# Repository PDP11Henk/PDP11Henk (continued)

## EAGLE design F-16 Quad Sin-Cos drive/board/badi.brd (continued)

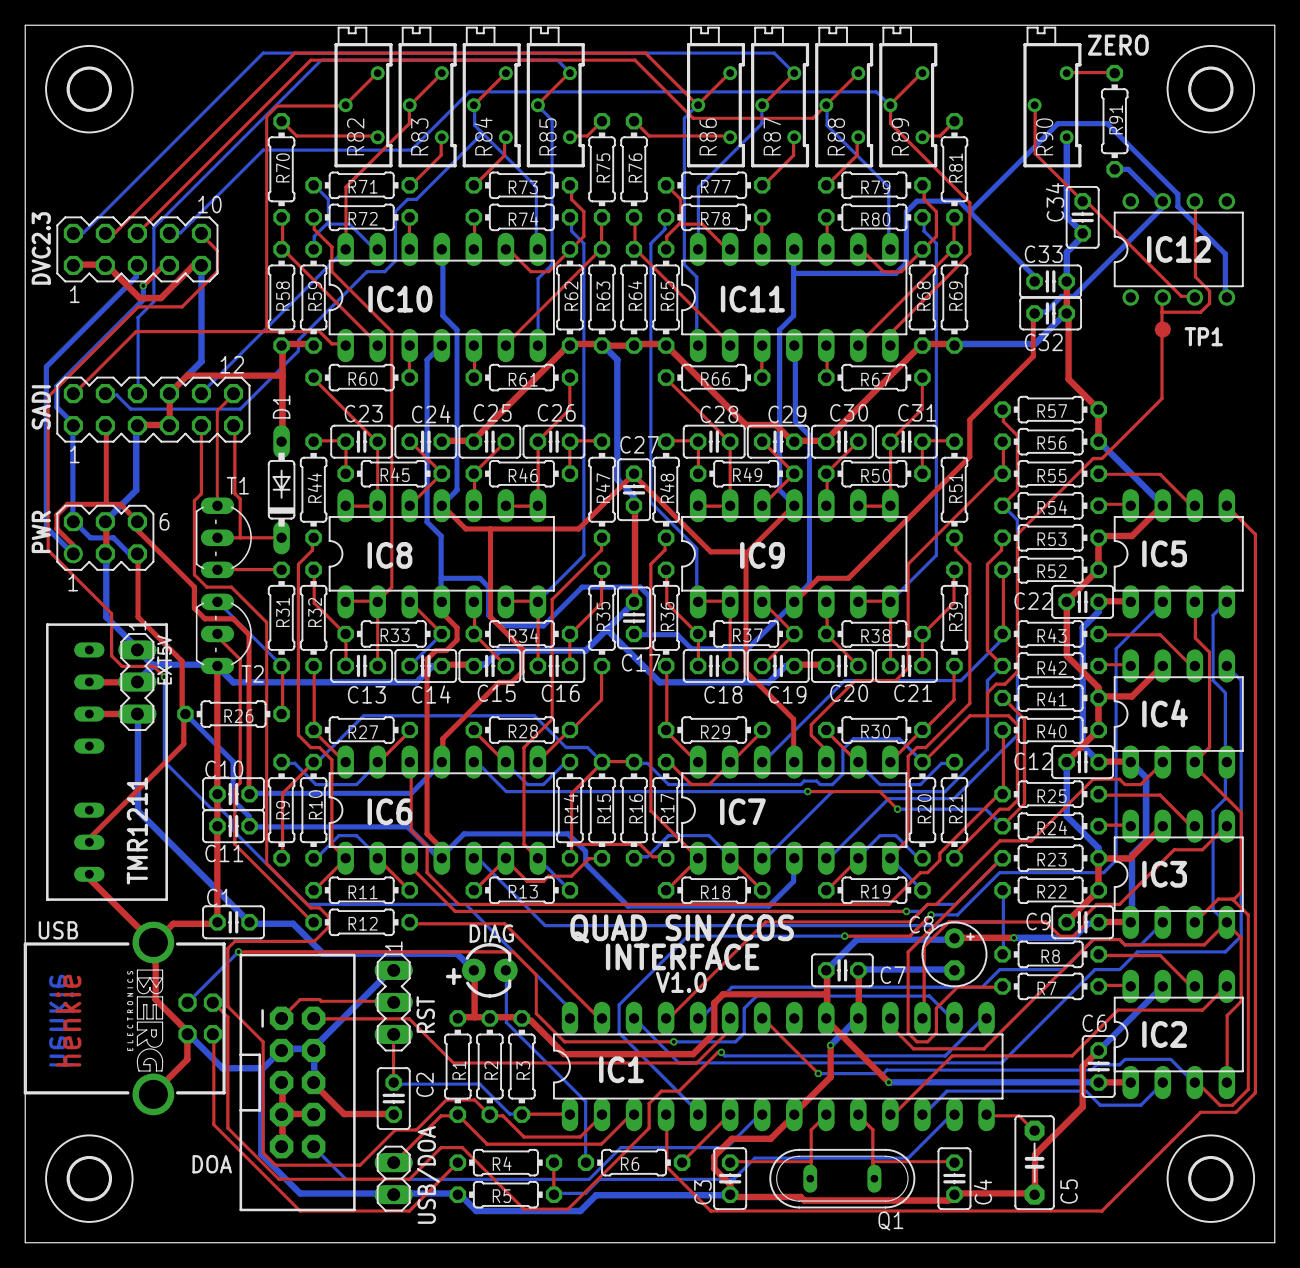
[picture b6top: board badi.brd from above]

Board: 2 copper layers, 99.0 x 96.5 mm, 156 parts (0 on the bottom side), 128 nets.

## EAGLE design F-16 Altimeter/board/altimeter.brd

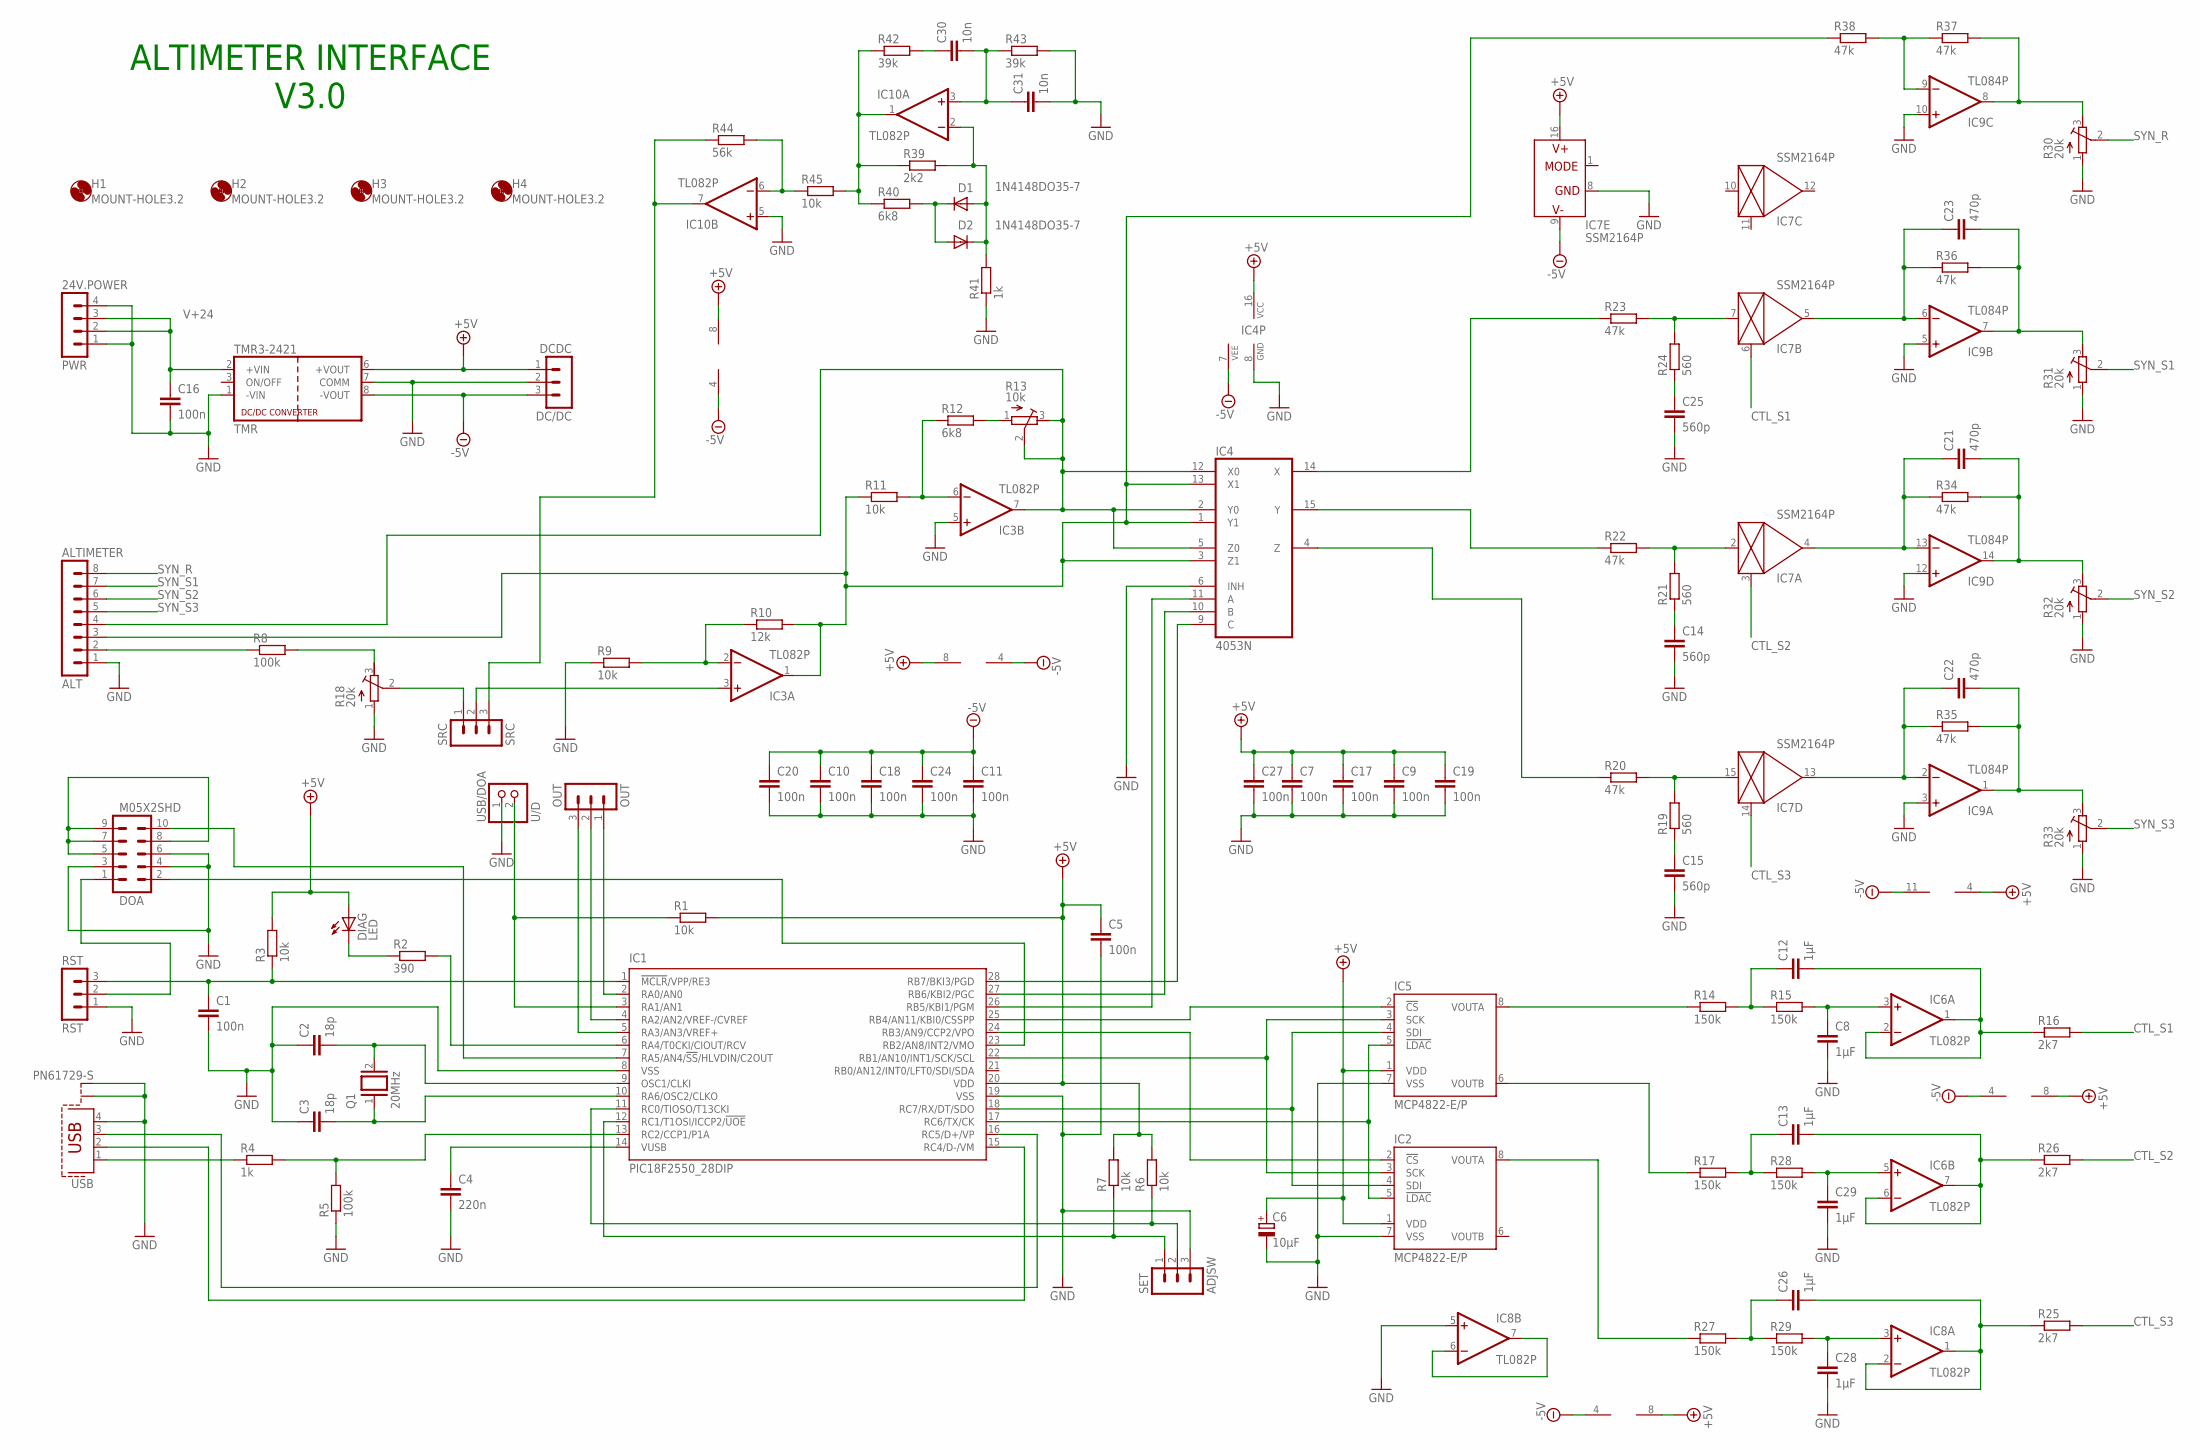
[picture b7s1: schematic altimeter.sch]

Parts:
24V.POWER: PWR; MA04-1
ADJSW: SET; MA03-1
ALTIMETER: ALT; MA08-1
C1, C5, C7, C9, C10, C11, C16, C17, C18, C19, C20, C24, C27: 100n; C025-025X050
C2, C3: 18p; C025-025X050
C4: 220n; C5B3
C6: 10µF; E2,5-5
C8, C12, C13, C26, C28, C29: 1µF; C025-025X050
C14, C15, C25: 560p; C025-025X050
C21, C22, C23: 470p; C025-025X050
C30, C31: 10n; C025-025X050
D1, D2: 1N4148DO35-7; DO35-7
DC/DC: DCDC; MA03-1
DIAG: LED; LED3MM
DOA: M05X2SHD; 2X5-SHROUDED
H1, H2, H3, H4: MOUNT-HOLE3.2; 3,2
IC1: PIC18F2550_28DIP; DIL28-3
IC2, IC5: MCP4822-E/P; DIL08
IC3, IC6, IC8, IC10: TL082P; DIL08
IC4: 4053N; DIL16
IC7: SSM2164P; DIL16
IC9: TL084P; DIL14
OUT: OUT; MA03-1
Q1: 20MHz; QS
R1, R3, R6, R7, R9, R11, R45: 10k; 0204/7
R2: 390; 0204/7
R4, R41: 1k; 0204/7
R5, R8: 100k; 0204/7
R10: 12k; 0204/7
R12, R40: 6k8; 0204/7
R13: 10k; RTRIM64Z
R14, R15, R17, R27, R28, R29: 150k; 0204/7
R16, R25, R26: 2k7; 0204/7
R18, R30, R31, R32, R33: 20k; RTRIM64Z
R19, R21, R24: 560; 0204/7
R20, R22, R23, R34, R35, R36, R37, R38: 47k; 0204/7
R39: 2k2; 0204/7
R42, R43: 39k; 0204/7
R44: 56k; 0204/7
RST: RST; MA03-1
SRC: SRC; MA03-1
TMR3-2421: TMR; TRACO_SIP-8
USB: PN61729-S
USB/DOA: U/D; 1X02

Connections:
+5V: C5.1, C6.+, C7.1, C9.1, C17.1, C19.1, C27.1, DC/DC.1, DIAG.A, IC1.20 (VDD), IC2.1 (VDD), IC3.8 (V+), IC4.16 (VCC), IC5.1 (VDD), IC6.8 (V+), IC7.16 (V+), IC8.8 (V+), IC9.4 (V+), IC10.8 (V+), R1.2, R3.2, R6.2, R7.2, TMR3-2421.6 (+VOUT)
-5V: C10.1, C11.1, C18.1, C20.1, C24.1, DC/DC.3, IC3.4 (V-), IC4.7 (VEE), IC6.4 (V-), IC7.9 (V-), IC8.4 (V-), IC9.11 (V-), IC10.4 (V-), TMR3-2421.8 (-VOUT)
CTL_S1: IC7.6 (CTRL), R16.2
CTL_S2: IC7.3 (CTRL), R26.2
CTL_S3: IC7.14 (CTRL), R25.2
GND: 24V.POWER.1, 24V.POWER.4, ADJSW.3, ALTIMETER.1, C1.2, C2.1, C3.1, C4.2, C5.2, C6.-, C7.2, C8.2, C9.2, C10.2, C11.2, C14.2, C15.2, C16.2, C17.2, C18.2, C19.2, C20.2, C24.2, C25.2, C27.2, C28.2, C29.2, C31.2, DC/DC.2, DOA.3, DOA.4, DOA.6, IC1.8 (VSS), IC1.19 (VSS), IC2.7 (VSS), IC3.5 (+IN), IC4.6 (INH), IC4.8 (GND), IC5.7 (VSS), IC7.8 (GND), IC8.5 (+IN), IC9.3 (+IN), IC9.5 (+IN), IC9.10 (+IN), IC9.12 (+IN), IC10.5 (+IN), R5.1, R9.1, R18.1 (A), R30.1 (A), R31.1 (A), R32.1 (A), R33.1 (A), R41.1, R43.2, RST.1, TMR3-2421.1 (-VIN), TMR3-2421.7 (COMM), USB.4, USB.S1, USB.S2, USB/DOA.1
MUX_A: IC1.26 (RB5/KBI1/PGM), IC4.11 (A)
MUX_B: IC1.27 (RB6/KBI2/PGC), IC4.10 (B)
MUX_C: IC1.28 (RB7/BKI3/PGD), IC4.9 (C)
unnamed: ALTIMETER.2, R8.1
unnamed: IC5.8 (VOUTA), R14.1
unnamed: IC9.8 (OUT), R30.3 (E), R37.2
unnamed: R8.2, R18.3 (E)
unnamed: IC5.6 (VOUTB), R17.1
unnamed: ADJSW.1, IC1.12 (RC1/T1OSI/ICCP2/!UOE), R7.1
unnamed: IC1.24 (RB3/AN9/CCP2/VPO), IC2.2 (!CS)
unnamed: R12.2, R13.1 (A)
unnamed: IC3.2 (-IN), R9.2, R10.1
unnamed: IC9.9 (-IN), R37.1, R38.2
unnamed: R18.2 (S), SRC.1
unnamed: IC3.3 (+IN), SRC.2
unnamed: ADJSW.2, IC1.11 (RC0/TIOSO/T13CKI), R6.1
unnamed: IC1.25 (RB4/AN11/KBI0/CSSPP), IC5.2 (!CS)
unnamed: C30.1, R42.2
unnamed: IC10.6 (-IN), R44.2, R45.1
unnamed: IC1.2 (RA0/AN0), OUT.1
unnamed: IC3.6 (-IN), R11.2, R12.1
unnamed: IC1.4 (RA2/AN2/VREF-/CVREF), OUT.2
unnamed: IC1.5 (RA3/AN3/VREF+), OUT.3
unnamed: IC10.7 (OUT), R44.1, SRC.3
unnamed: C12.2, IC6.1 (OUT), IC6.2 (-IN), R16.1
unnamed: IC1.17 (RC6/TX/CK), IC2.5 (!LDAC), IC5.5 (!LDAC)
unnamed: IC1.18 (RC7/RX/DT/SDO), IC2.4 (SDI), IC5.4 (SDI)
unnamed: IC10.1 (OUT), R39.1, R40.1, R42.1, R45.2
unnamed: ALTIMETER.4, IC3.7 (OUT), IC4.2 (Y0), IC4.5 (Z0), IC4.12 (X0), R13.2 (S), R13.3 (E)
unnamed: C8.1, IC6.3 (+IN), R15.2
unnamed: C30.2, C31.1, IC10.3 (+IN), R43.1
unnamed: D1.C, D2.A, R40.2
unnamed: C12.1, R14.2, R15.1
unnamed: D1.A, D2.C, IC10.2 (-IN), R39.2, R41.2
unnamed: IC7.7 (IN), R23.2, R24.2
unnamed: C26.2, IC8.1 (OUT), IC8.2 (-IN), R25.1
unnamed: IC7.2 (IN), R21.2, R22.2
unnamed: C28.1, IC8.3 (+IN), R29.2
unnamed: IC7.15 (IN), R19.2, R20.2
unnamed: C25.1, R24.1
unnamed: C14.1, R21.1
unnamed: C15.1, R19.1
unnamed: C13.2, IC6.6 (-IN), IC6.7 (OUT), R26.1
unnamed: C13.1, R17.2, R28.1
unnamed: IC1.22 (RB1/AN10/INT1/SCK/SCL), IC2.3 (SCK), IC5.3 (SCK)
unnamed: C29.1, IC6.5 (+IN), R28.2
unnamed: C26.1, R27.2, R29.1
unnamed: IC2.8 (VOUTA), R27.1
unnamed: IC8.6 (-IN), IC8.7 (OUT)
unnamed: C4.1, IC1.14 (VUSB)
unnamed: IC1.16 (RC5/D+/VP), USB.3
unnamed: C23.1, IC7.5 (OUT), IC9.6 (-IN), R36.1
unnamed: C23.2, IC9.7 (OUT), R31.3 (E), R36.2
unnamed: C21.1, IC7.4 (OUT), IC9.13 (-IN), R34.1
unnamed: C21.2, IC9.14 (OUT), R32.3 (E), R34.2
unnamed: C22.1, IC7.13 (OUT), IC9.2 (-IN), R35.1
unnamed: C22.2, IC9.1 (OUT), R33.3 (E), R35.2
unnamed: IC1.15 (RC4/D-/VM), USB.2
unnamed: R4.1, USB.1
unnamed: IC1.13 (RC2/CCP1/P1A), R4.2, R5.2
unnamed: DOA.1, RST.2
unnamed: C3.2, IC1.10 (RA6/OSC2/CLKO), Q1.1
unnamed: C2.2, IC1.9 (OSC1/CLKI), Q1.2
unnamed: C1.1, IC1.1 (!MCLR!/VPP/RE3), R3.1, RST.3
unnamed: DOA.5, DOA.7, DOA.8, DOA.9
unnamed: DOA.2, IC1.23 (RB2/AN8/INT2/VMO)
unnamed: DIAG.K (C), R2.1
unnamed: IC1.6 (RA4/T0CKI/CIOUT/RCV), R2.2
unnamed: DOA.10, IC1.7 (RA5/AN4/!SS!/HLVDIN/C2OUT)
unnamed: IC1.3 (RA1/AN1), R1.1, USB/DOA.2
REF_S1: IC4.14 (X), R23.1
REF_S2: IC4.15 (Y), R22.1
REF_S3: IC4.4 (Z), R20.1
SIN: ALTIMETER.3, IC3.1 (OUT), IC4.1 (Y1), IC4.3 (Z1), IC4.13 (X1), R10.2, R11.1, R38.1
SYN_R: ALTIMETER.8, R30.2 (S)
SYN_S1: ALTIMETER.7, R31.2 (S)
SYN_S2: ALTIMETER.6, R32.2 (S)
SYN_S3: ALTIMETER.5, R33.2 (S)
V+24: 24V.POWER.2, 24V.POWER.3, C16.1, TMR3-2421.2 (+VIN)

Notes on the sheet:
ALTIMETER INTERFACE V3.0

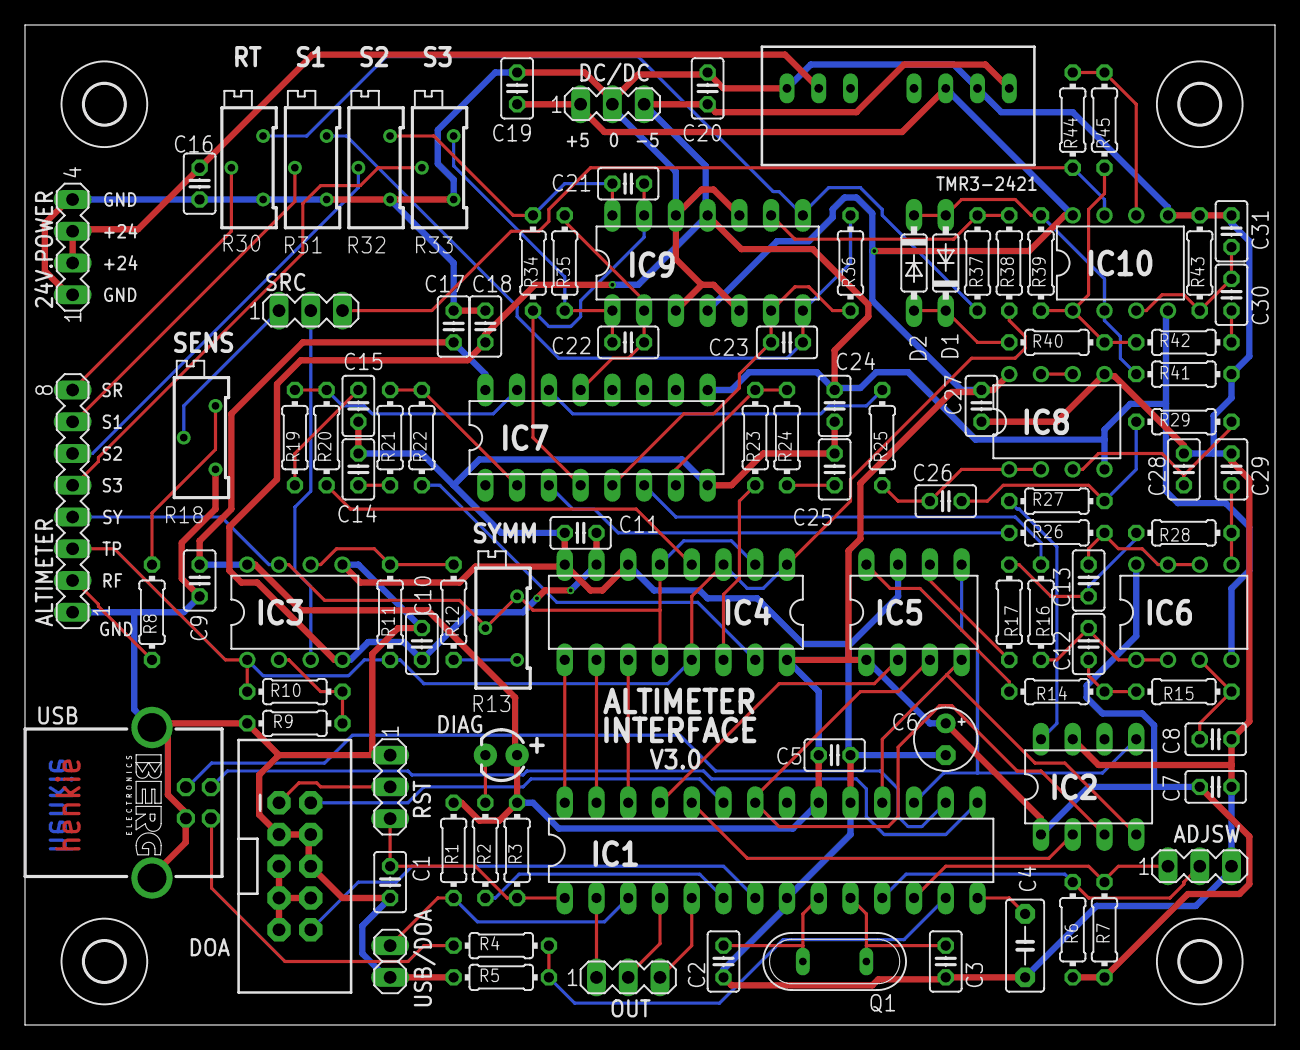
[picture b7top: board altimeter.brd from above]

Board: 2 copper layers, 100.0 x 80.0 mm, 105 parts (0 on the bottom side), 85 nets.

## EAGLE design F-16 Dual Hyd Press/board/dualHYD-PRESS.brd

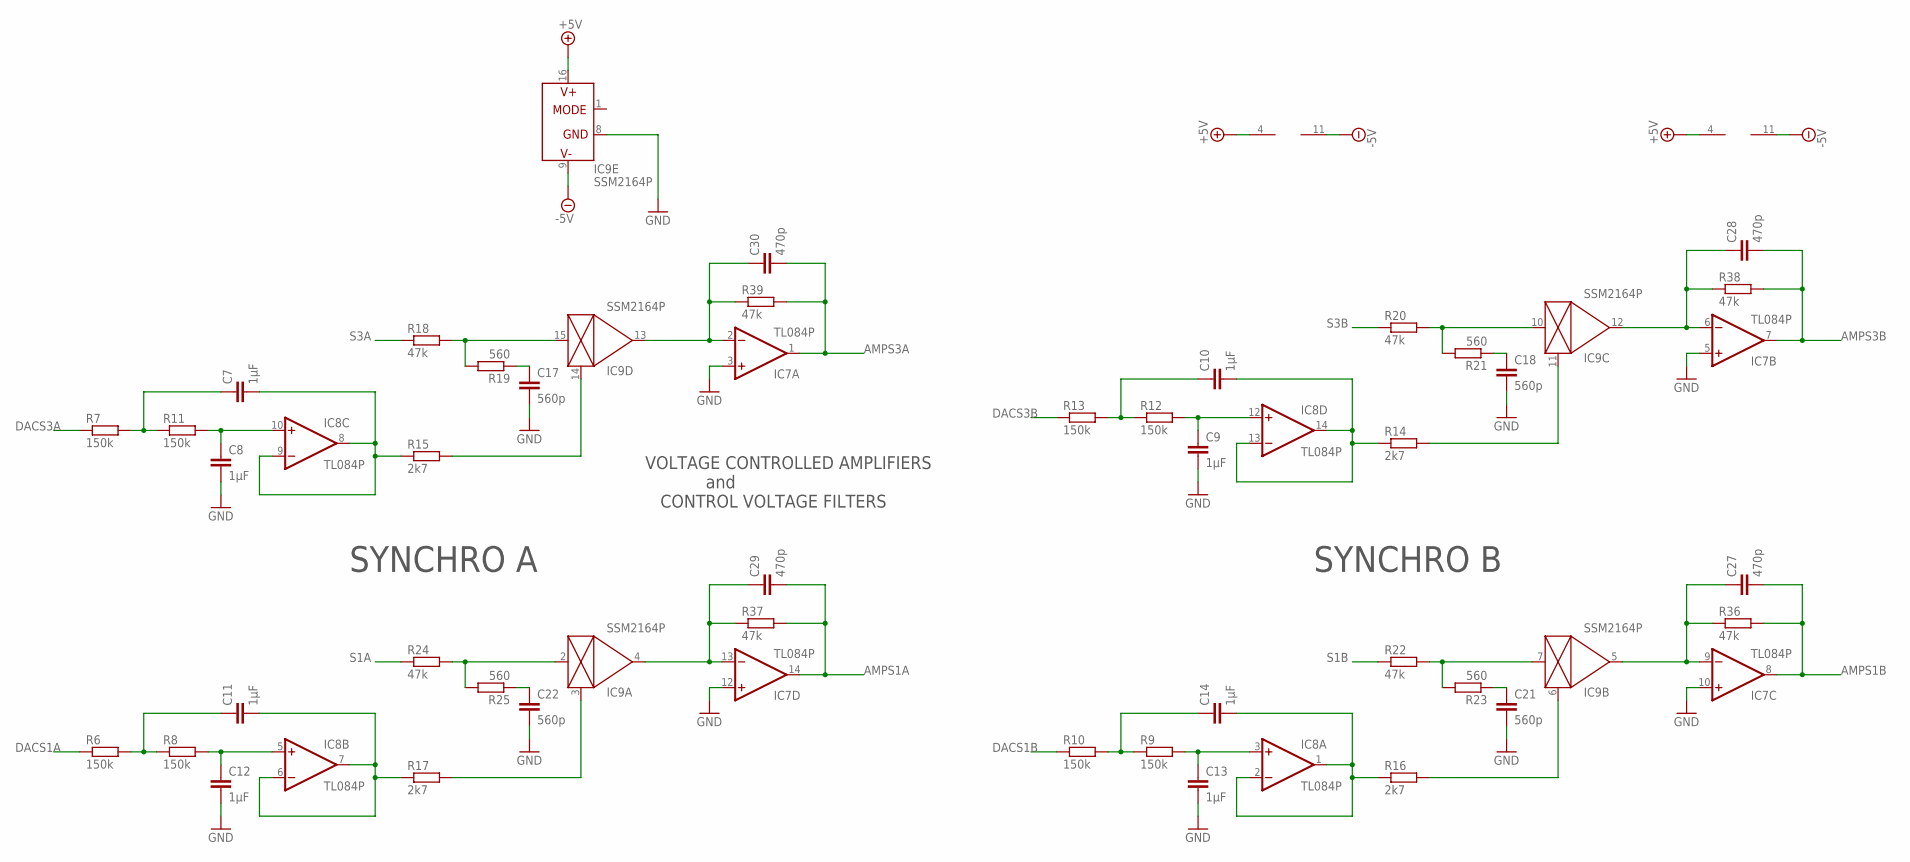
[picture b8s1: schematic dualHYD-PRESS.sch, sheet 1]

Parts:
C7, C8, C9, C10, C11, C12, C13, C14: 1µF; C025-025X050
C17, C18, C21, C22: 560p; C025-025X050
C27, C28, C29, C30: 470p; C025-025X050
IC7, IC8: TL084P; DIL14
IC9: SSM2164P; DIL16
R6, R7, R8, R9, R10, R11, R12, R13: 150k; 0207/7
R14, R15, R16, R17: 2k7; 0207/7
R18, R20, R22, R24, R36, R37, R38, R39: 47k; 0207/7
R19, R21, R23, R25: 560; 0207/7

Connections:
+5V: IC7.4 (V+), IC8.4 (V+), IC9.16 (V+); also elsewhere on the board
-5V: IC7.11 (V-), IC8.11 (V-), IC9.9 (V-); also elsewhere on the board
AMPS1A: C29.2, IC7.14 (OUT), R37.2; also elsewhere on the board
AMPS1B: C27.2, IC7.8 (OUT), R36.2; also elsewhere on the board
AMPS3A: C30.2, IC7.1 (OUT), R39.2; also elsewhere on the board
AMPS3B: C28.2, IC7.7 (OUT), R38.2; also elsewhere on the board
BXCF: C10.2, IC8.13 (-IN), IC8.14 (OUT), R14.1
BZCF: C11.2, IC8.6 (-IN), IC8.7 (OUT), R17.1
DACS1A: R6.1; also elsewhere on the board
DACS1B: R10.1; also elsewhere on the board
DACS3A: R7.1; also elsewhere on the board
DACS3B: R13.1; also elsewhere on the board
GND: C8.2, C9.2, C12.2, C13.2, C17.2, C18.2, C21.2, C22.2, IC7.3 (+IN), IC7.5 (+IN), IC7.10 (+IN), IC7.12 (+IN), IC9.8 (GND); also elsewhere on the board
M1XCF: C14.2, IC8.1 (OUT), IC8.2 (-IN), R16.1
M1YCF: C7.2, IC8.8 (OUT), IC8.9 (-IN), R15.1
unnamed: C14.1, R9.1, R10.2
unnamed: IC9.3 (CTRL), R17.2
unnamed: C13.1, IC8.3 (+IN), R9.2
unnamed: C11.1, R6.2, R8.1
unnamed: IC9.14 (CTRL), R15.2
unnamed: C12.1, IC8.5 (+IN), R8.2
unnamed: C8.1, IC8.10 (+IN), R11.2
unnamed: C7.1, R7.2, R11.1
unnamed: C10.1, R12.1, R13.2
unnamed: C9.1, IC8.12 (+IN), R12.2
unnamed: IC9.11 (CTRL), R14.2
unnamed: IC9.6 (CTRL), R16.2
unnamed: IC9.10 (IN), R20.2, R21.2
unnamed: C18.1, R21.1
unnamed: IC9.15 (IN), R18.2, R19.2
unnamed: C17.1, R19.1
unnamed: IC9.7 (IN), R22.2, R23.2
unnamed: C21.1, R23.1
unnamed: IC9.2 (IN), R24.2, R25.2
unnamed: C22.1, R25.1
unnamed: C29.1, IC7.13 (-IN), IC9.4 (OUT), R37.1
unnamed: C30.1, IC7.2 (-IN), IC9.13 (OUT), R39.1
unnamed: C28.1, IC7.6 (-IN), IC9.12 (OUT), R38.1
unnamed: C27.1, IC7.9 (-IN), IC9.5 (OUT), R36.1
S1A: R24.1; also elsewhere on the board
S1B: R22.1; also elsewhere on the board
S3A: R18.1; also elsewhere on the board
S3B: R20.1; also elsewhere on the board

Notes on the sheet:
VOLTAGE CONTROLLED AMPLIFIERS and CONTROL VOLTAGE FILTERS
SYNCHRO A
SYNCHRO B

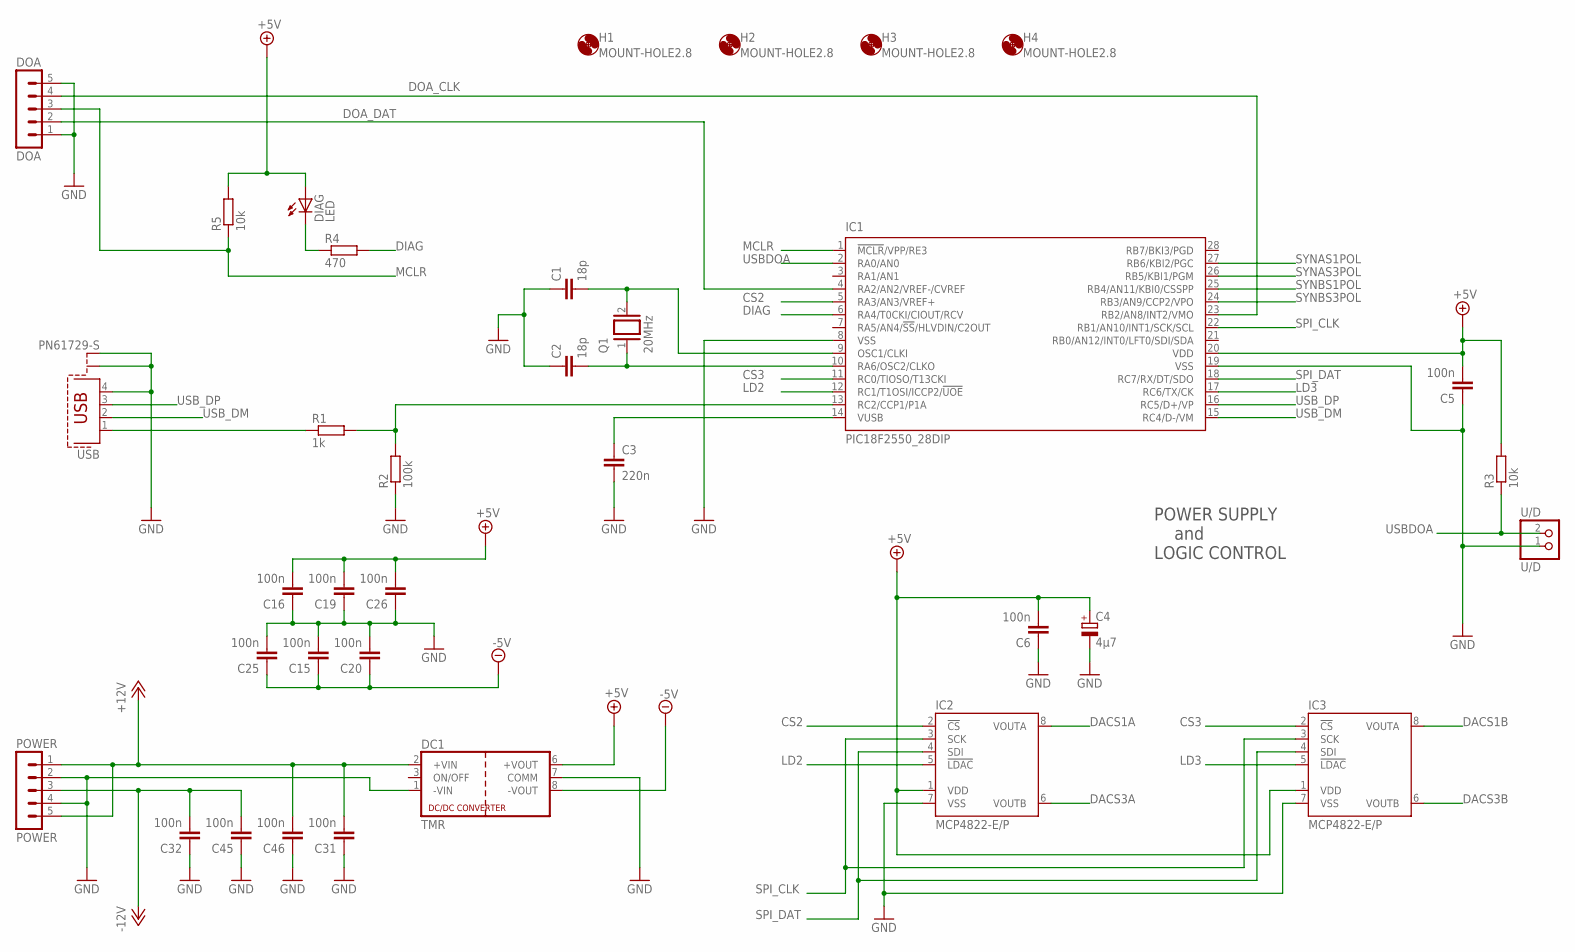
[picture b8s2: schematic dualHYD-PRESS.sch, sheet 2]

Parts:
C1, C2: 18p; C025-025X050
C3: 220n; C5B3
C4: 4µ7; E2,5-5
C5, C6, C15, C16, C19, C20, C25, C26, C31, C32, C45, C46: 100n; C025-025X050
DC1: TMR; TRACO_SIP-8
DIAG: LED; LED3MM
DOA: DOA; MA05-1
H1, H2, H3, H4: MOUNT-HOLE2.8; 2,8
IC1: PIC18F2550_28DIP; DIL28-3
IC2, IC3: MCP4822-E/P; DIL08
POWER: POWER; MA05-1
Q1: 20MHz; QS
R1: 1k; 0204/7
R2: 100k; 0204/7
R3, R5: 10k; 0204/7
R4: 470; 0204/7
U/D: U/D; 1X02
USB: PN61729-S

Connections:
+5V: C4.+, C5.2, C6.2, C16.2, C19.2, C26.2, DC1.6 (+VOUT), DIAG.A, IC1.20 (VDD), IC2.1 (VDD), IC3.1 (VDD), R3.2, R5.2; also elsewhere on the board
+12V: C31.2, C46.2, DC1.2 (+VIN), POWER.1, POWER.5; also elsewhere on the board
-5V: C15.1, C20.1, C25.1, DC1.8 (-VOUT); also elsewhere on the board
-12V: C32.2, C45.2, POWER.3; also elsewhere on the board
CS2: IC1.5 (RA3/AN3/VREF+), IC2.2 (!CS)
CS3: IC1.11 (RC0/TIOSO/T13CKI), IC3.2 (!CS)
DACS1A: IC2.8 (VOUTA); also elsewhere on the board
DACS1B: IC3.8 (VOUTA); also elsewhere on the board
DACS3A: IC2.6 (VOUTB); also elsewhere on the board
DACS3B: IC3.6 (VOUTB); also elsewhere on the board
DIAG: IC1.6 (RA4/T0CKI/CIOUT/RCV), R4.2
DOA_CLK: DOA.4, IC1.23 (RB2/AN8/INT2/VMO)
DOA_DAT: DOA.2, IC1.4 (RA2/AN2/VREF-/CVREF)
GND: C1.1, C2.1, C3.2, C4.-, C5.1, C6.1, C15.2, C16.1, C19.1, C20.2, C25.2, C26.1, C31.1, C32.1, C45.1, C46.1, DC1.1 (-VIN), DC1.7 (COMM), DOA.1, DOA.5, IC1.8 (VSS), IC1.19 (VSS), IC2.7 (VSS), IC3.7 (VSS), POWER.2, POWER.4, R2.1, U/D.1, USB.4, USB.S1, USB.S2; also elsewhere on the board
LD2: IC1.12 (RC1/T1OSI/ICCP2/!UOE), IC2.5 (!LDAC)
LD3: IC1.17 (RC6/TX/CK), IC3.5 (!LDAC)
MCLR: DOA.3, IC1.1 (!MCLR!/VPP/RE3), R5.1
unnamed: R1.1, USB.1
unnamed: IC1.13 (RC2/CCP1/P1A), R1.2, R2.2
unnamed: C2.2, IC1.10 (RA6/OSC2/CLKO), Q1.1
unnamed: C1.2, IC1.9 (OSC1/CLKI), Q1.2
unnamed: DIAG.K (C), R4.1
unnamed: C3.1, IC1.14 (VUSB)
SPI_CLK: IC1.22 (RB1/AN10/INT1/SCK/SCL), IC2.3 (SCK), IC3.3 (SCK)
SPI_DAT: IC1.18 (RC7/RX/DT/SDO), IC2.4 (SDI), IC3.4 (SDI)
SYNAS1POL: IC1.27 (RB6/KBI2/PGC); also elsewhere on the board
SYNAS3POL: IC1.26 (RB5/KBI1/PGM); also elsewhere on the board
SYNBS1POL: IC1.25 (RB4/AN11/KBI0/CSSPP); also elsewhere on the board
SYNBS3POL: IC1.24 (RB3/AN9/CCP2/VPO); also elsewhere on the board
USBDOA: IC1.2 (RA0/AN0), R3.1, U/D.2
USB_DM: IC1.15 (RC4/D-/VM), USB.2
USB_DP: IC1.16 (RC5/D+/VP), USB.3

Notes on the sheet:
POWER SUPPLY and LOGIC CONTROL

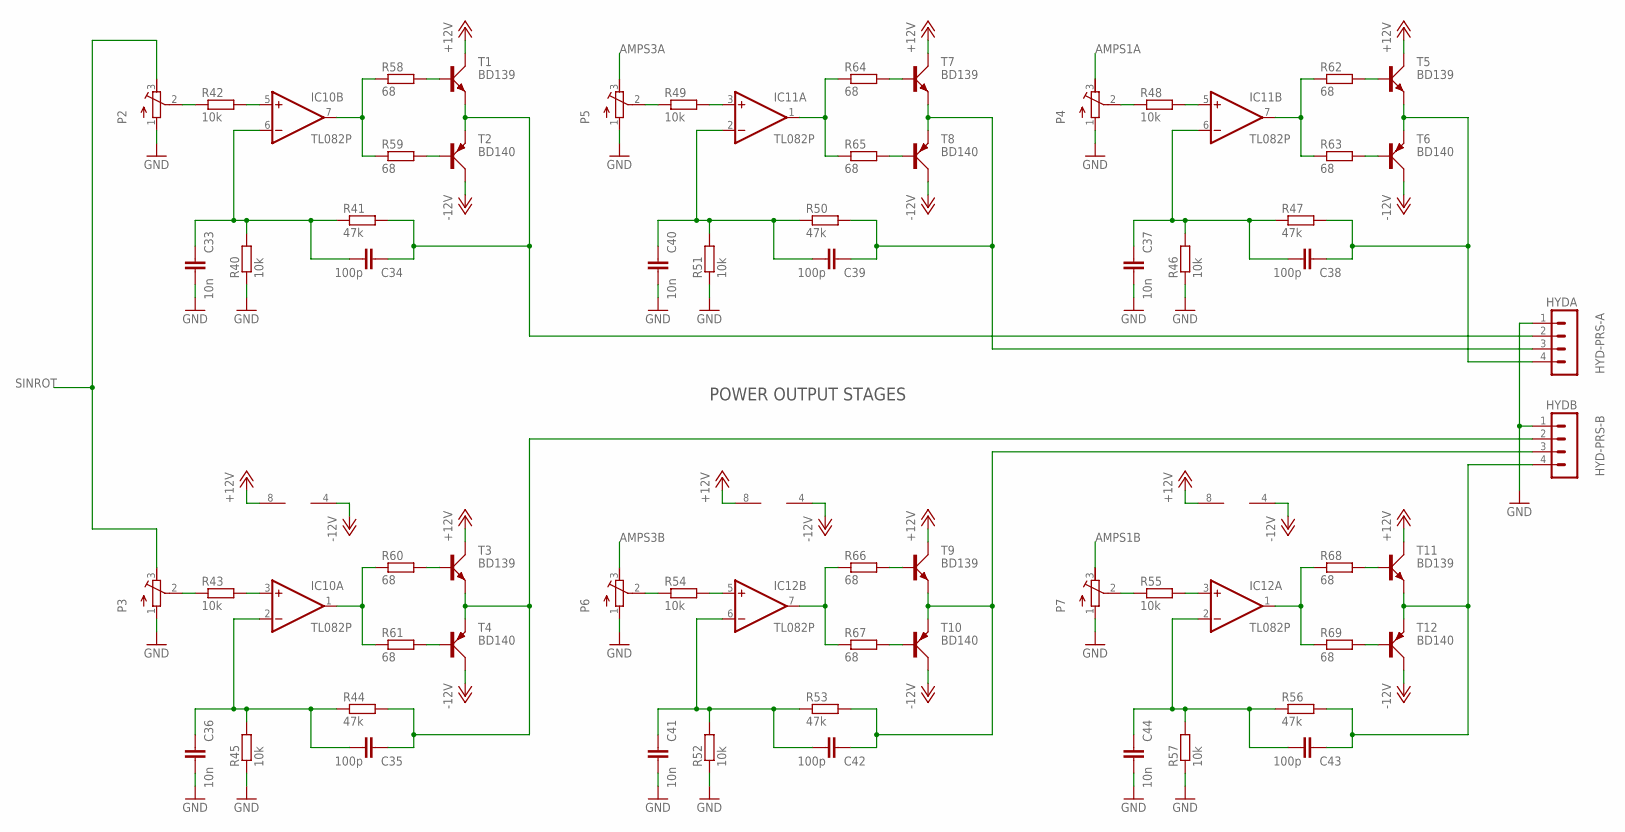
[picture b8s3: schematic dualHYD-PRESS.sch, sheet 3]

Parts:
C33, C36, C37, C40, C41, C44: 10n; C025-025X050
C34, C35, C38, C39, C42, C43: 100p; C025-025X050
HYD-PRS-A: HYDA; MA04-1
HYD-PRS-B: HYDB; MA04-1
IC10, IC11, IC12: TL082P; DIL08
P2, P3, P4, P5, P6, P7: R-TRIMM64Y; RTRIM64Y
R40, R42, R43, R45, R46, R48, R49, R51, R52, R54, R55, R57: 10k; 0204/7
R41, R44, R47, R50, R53, R56: 47k; 0204/7
R58, R59, R60, R61, R62, R63, R64, R65, R66, R67, R68, R69: 68; 0204/7
T1, T3, T5, T7, T9, T11: BD139; TO126AV
T2, T4, T6, T8, T10, T12: BD140; TO126AV

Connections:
+12V: IC10.8 (V+), IC11.8 (V+), IC12.8 (V+), T1.C, T3.C, T5.C, T7.C, T9.C, T11.C; also elsewhere on the board
-12V: IC10.4 (V-), IC11.4 (V-), IC12.4 (V-), T2.C, T4.C, T6.C, T8.C, T10.C, T12.C; also elsewhere on the board
AMPS1A: P4.3 (E); also elsewhere on the board
AMPS1B: P7.3 (E); also elsewhere on the board
AMPS3A: P5.3 (E); also elsewhere on the board
AMPS3B: P6.3 (E); also elsewhere on the board
GND: C33.1, C36.1, C37.1, C40.1, C41.1, C44.1, HYD-PRS-A.1, HYD-PRS-B.1, P2.1 (A), P3.1 (A), P4.1 (A), P5.1 (A), P6.1 (A), P7.1 (A), R40.1, R45.1, R46.1, R51.1, R52.1, R57.1; also elsewhere on the board
unnamed: R58.2, T1.B
unnamed: P2.2 (S), R42.1
unnamed: R59.2, T2.B
unnamed: IC10.5 (+IN), R42.2
unnamed: R60.2, T3.B
unnamed: R61.2, T4.B
unnamed: P6.2 (S), R54.1
unnamed: R62.2, T5.B
unnamed: R63.2, T6.B
unnamed: C38.2, HYD-PRS-A.4, R47.2, T5.E, T6.E
unnamed: C42.2, HYD-PRS-B.3, R53.2, T9.E, T10.E
unnamed: R67.2, T10.B
unnamed: R66.2, T9.B
unnamed: R64.2, T7.B
unnamed: R65.2, T8.B
unnamed: C35.2, HYD-PRS-B.2, R44.2, T3.E, T4.E
unnamed: R68.2, T11.B
unnamed: R69.2, T12.B
unnamed: IC10.3 (+IN), R43.2
unnamed: C43.2, HYD-PRS-B.4, R56.2, T11.E, T12.E
unnamed: IC12.7 (OUT), R66.1, R67.1
unnamed: IC12.1 (OUT), R68.1, R69.1
unnamed: IC11.7 (OUT), R62.1, R63.1
unnamed: P3.2 (S), R43.1
unnamed: IC11.1 (OUT), R64.1, R65.1
unnamed: IC10.7 (OUT), R58.1, R59.1
unnamed: P5.2 (S), R49.1
unnamed: IC11.3 (+IN), R49.2
unnamed: P4.2 (S), R48.1
unnamed: IC11.5 (+IN), R48.2
unnamed: IC10.1 (OUT), R60.1, R61.1
unnamed: IC12.5 (+IN), R54.2
unnamed: C33.2, C34.1, IC10.6 (-IN), R40.2, R41.1
unnamed: P7.2 (S), R55.1
unnamed: C35.1, C36.2, IC10.2 (-IN), R44.1, R45.2
unnamed: C37.2, C38.1, IC11.6 (-IN), R46.2, R47.1
unnamed: IC12.3 (+IN), R55.2
unnamed: C39.1, C40.2, IC11.2 (-IN), R50.1, R51.2
unnamed: C41.2, C42.1, IC12.6 (-IN), R52.2, R53.1
unnamed: C43.1, C44.2, IC12.2 (-IN), R56.1, R57.2
unnamed: C39.2, HYD-PRS-A.3, R50.2, T7.E, T8.E
unnamed: C34.2, HYD-PRS-A.2, R41.2, T1.E, T2.E
SINROT: P2.3 (E), P3.3 (E); also elsewhere on the board

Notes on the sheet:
POWER OUTPUT STAGES

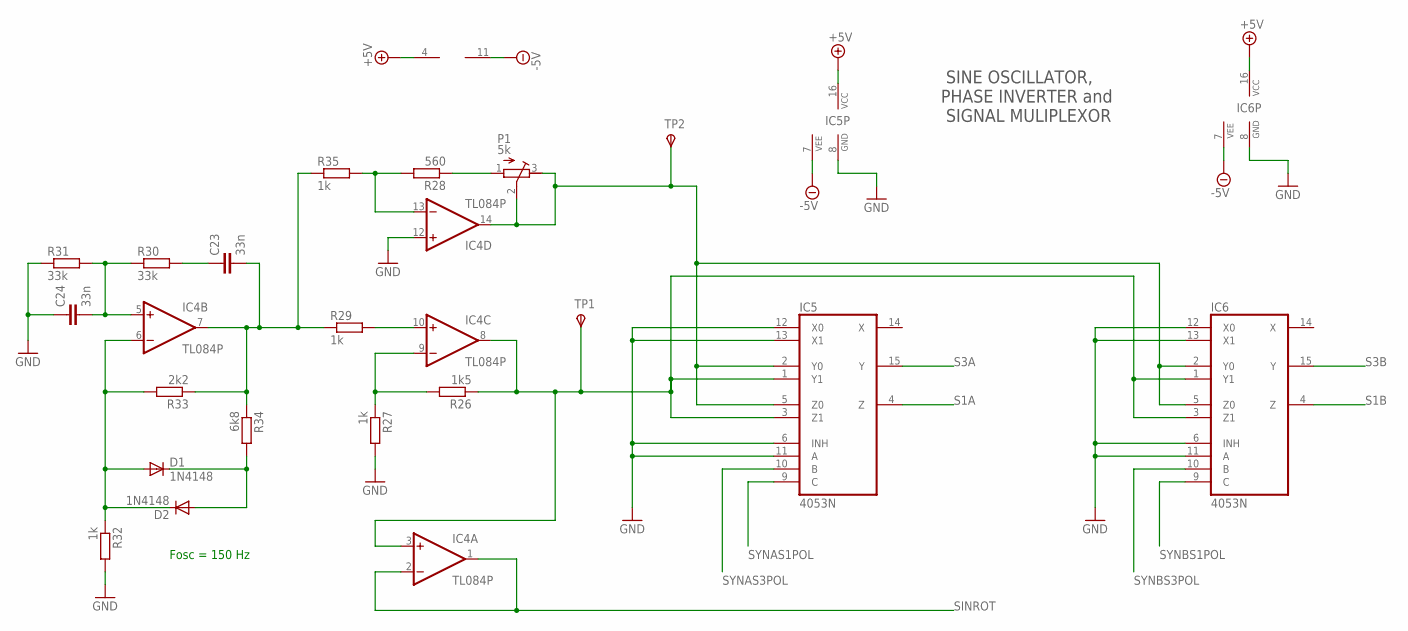
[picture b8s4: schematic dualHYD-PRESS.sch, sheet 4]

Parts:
C23, C24: 33n; C025-024X044
D1, D2: 1N4148; DO35-7
IC4: TL084P; DIL14
IC5, IC6: 4053N; DIL16
P1: 5k; RTRIM64Y
R26: 1k5; 0204/7
R27, R29, R32, R35: 1k; 0204/7
R28: 560; 0204/7
R30, R31: 33k; 0204/7
R33: 2k2; 0204/7
R34: 6k8; 0204/7
TP1, TP2: TPSPAD1-17; P1-17

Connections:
+5V: IC4.4 (V+), IC5.16 (VCC), IC6.16 (VCC); also elsewhere on the board
-5V: IC4.11 (V-), IC5.7 (VEE), IC6.7 (VEE); also elsewhere on the board
GND: C24.1, IC4.12 (+IN), IC5.6 (INH), IC5.8 (GND), IC5.11 (A), IC5.12 (X0), IC5.13 (X1), IC6.6 (INH), IC6.8 (GND), IC6.11 (A), IC6.12 (X0), IC6.13 (X1), R27.2, R31.1, R32.2; also elsewhere on the board
unnamed: D1.A, D2.C, IC4.6 (-IN), R32.1, R33.2
unnamed: D1.C, D2.A, R34.2
unnamed: IC4.9 (-IN), R26.2, R27.1
unnamed: IC4.13 (-IN), R28.2, R35.2
unnamed: IC4.10 (+IN), R29.2
unnamed: IC4.3 (+IN), IC4.8 (OUT), IC5.1 (Y1), IC5.3 (Z1), IC6.1 (Y1), IC6.3 (Z1), R26.1, TP1.TP
unnamed: C23.2, IC4.7 (OUT), R29.1, R33.1, R34.1, R35.1
unnamed: P1.1 (A), R28.1
unnamed: C23.1, R30.2
unnamed: IC4.14 (OUT), IC5.2 (Y0), IC5.5 (Z0), IC6.2 (Y0), IC6.5 (Z0), P1.2 (S), P1.3 (E), TP2.TP
unnamed: C24.2, IC4.5 (+IN), R30.1, R31.2
S1A: IC5.4 (Z); also elsewhere on the board
S1B: IC6.4 (Z); also elsewhere on the board
S3A: IC5.15 (Y); also elsewhere on the board
S3B: IC6.15 (Y); also elsewhere on the board
SINROT: IC4.1 (OUT), IC4.2 (-IN); also elsewhere on the board
SYNAS1POL: IC5.9 (C); also elsewhere on the board
SYNAS3POL: IC5.10 (B); also elsewhere on the board
SYNBS1POL: IC6.9 (C); also elsewhere on the board
SYNBS3POL: IC6.10 (B); also elsewhere on the board

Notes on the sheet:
SINE OSCILLATOR, PHASE INVERTER and SIGNAL MULIPLEXOR
Fosc = 150 Hz

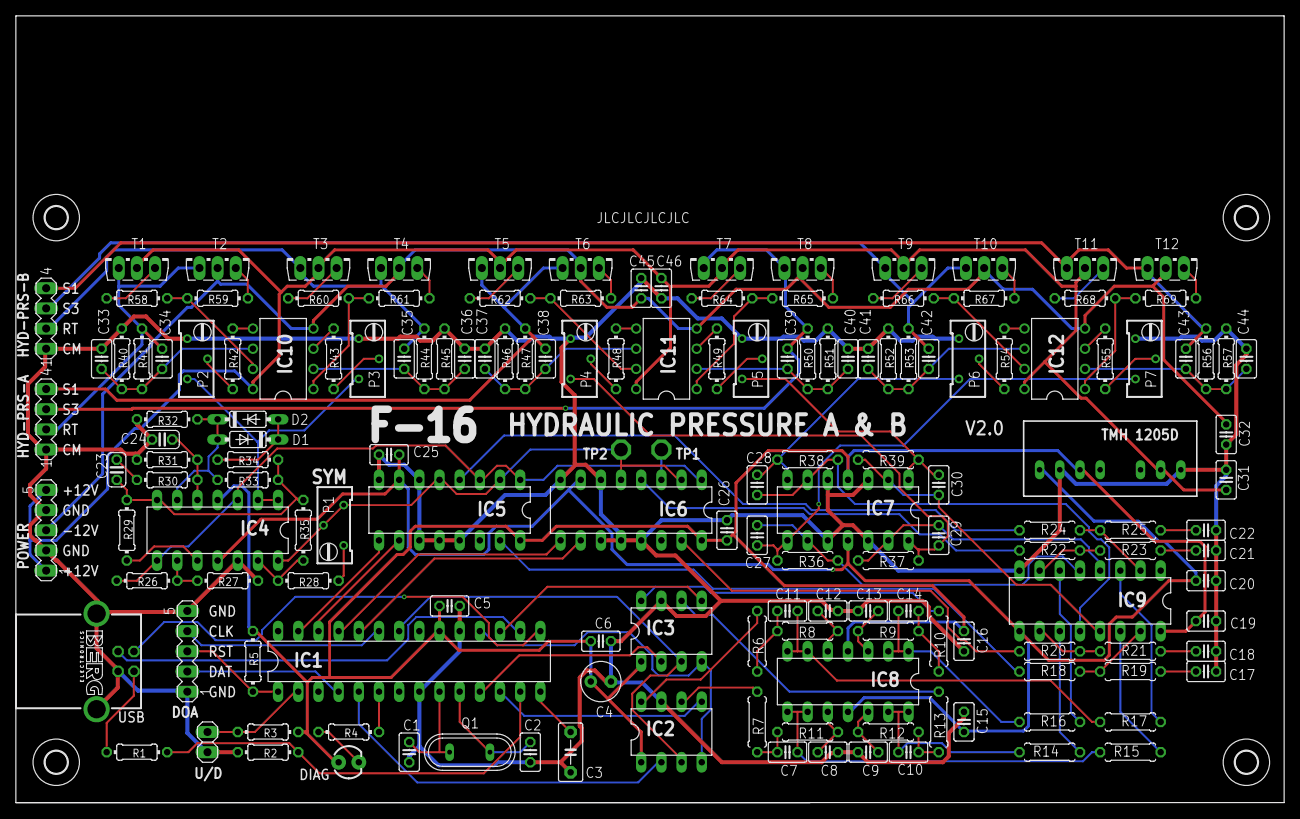
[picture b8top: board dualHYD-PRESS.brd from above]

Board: 2 copper layers, 159.7 x 99.1 mm, 163 parts (0 on the bottom side), 122 nets.

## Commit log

2021-06-03 First commit. PIC source code and PIC hardware design to interface a DIGITAL PC05 papertape reader/punch to a serial port instead of the PC11 PDP-11 interface.
2021-06-03 Initial commit. PIC control for the DX11 front panel with 144 lamps via a serial link. Firmware holds the PIC source code. Testappl holds the test application written in Python 3.6. Board has the Eag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
2021-06-03 Renamed folder to indicate what it is.
2021-06-03 Initial commit of the F-16 HSI interface.
2021-06-03 Initial commit F-16 ADI interface.
2021-06-03 Initial commit F-16 FFI interface
2021-06-04 Initial commit of the Hydraulic Pressure indicators interface
2021-06-04 Initial commit F-16 altimeter interface
2021-06-04 Initial commit F-16 Quad Sin/Cos drive interface
2021-06-04 Initial commit X27 micro-stepper interface
2021-06-20 First version of the ROSCO M68k "Blinkenlight Console".
2021-06-26 Added pictures of the assembled boards.
2021-07-01 Toggle switches could not be read, data bus direction equation had an error.
2021-07-01 Added the PCBs for the frontpanel LEDs and switches.
